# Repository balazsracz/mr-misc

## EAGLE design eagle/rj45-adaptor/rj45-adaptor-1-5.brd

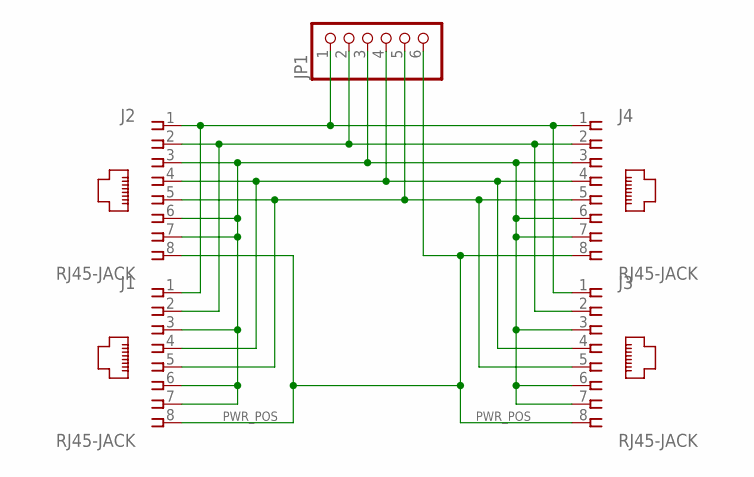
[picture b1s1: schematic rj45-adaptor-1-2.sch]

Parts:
J1, J2, J3, J4: RJ45-JACK; RJ45-PULSE-E5J88
JP1: PINHD-1X6; 1X06

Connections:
ALT1: J1.4, J2.4, J3.4, J4.4, JP1.4
ALT2: J1.5, J2.5, J3.5, J4.5, JP1.5
CANH: J1.1, J2.1, J3.1, J4.1, JP1.1
CANL: J1.2, J2.2, J3.2, J4.2, JP1.2
GND: J1.3, J1.6, J1.7, J2.3, J2.6, J2.7, J3.3, J3.6, J3.7, J4.3, J4.6, J4.7, JP1.3
PWR_POS: J1.8, J2.8, J3.8, J4.8, JP1.6

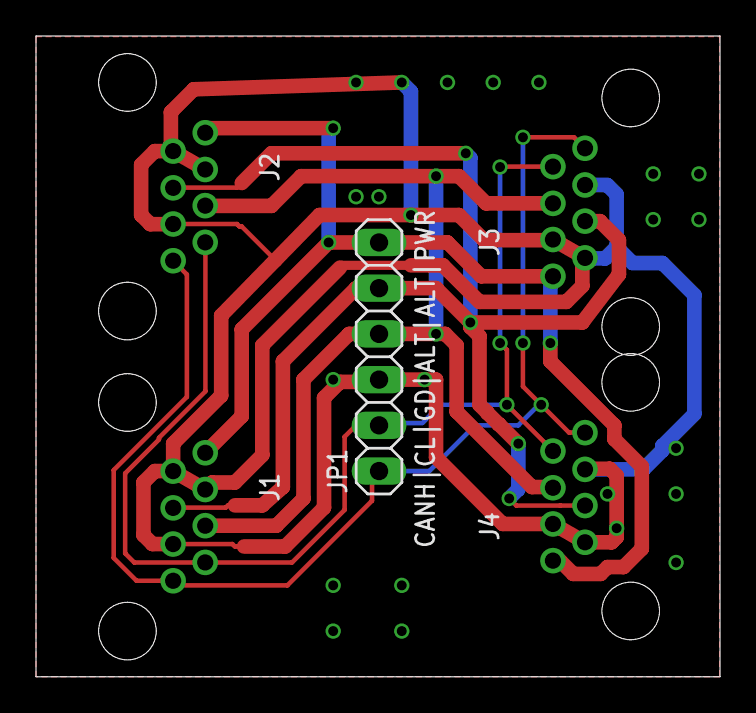
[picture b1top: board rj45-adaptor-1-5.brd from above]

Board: 2 copper layers, 38.0 x 35.6 mm, 5 parts (0 on the bottom side), 6 nets.

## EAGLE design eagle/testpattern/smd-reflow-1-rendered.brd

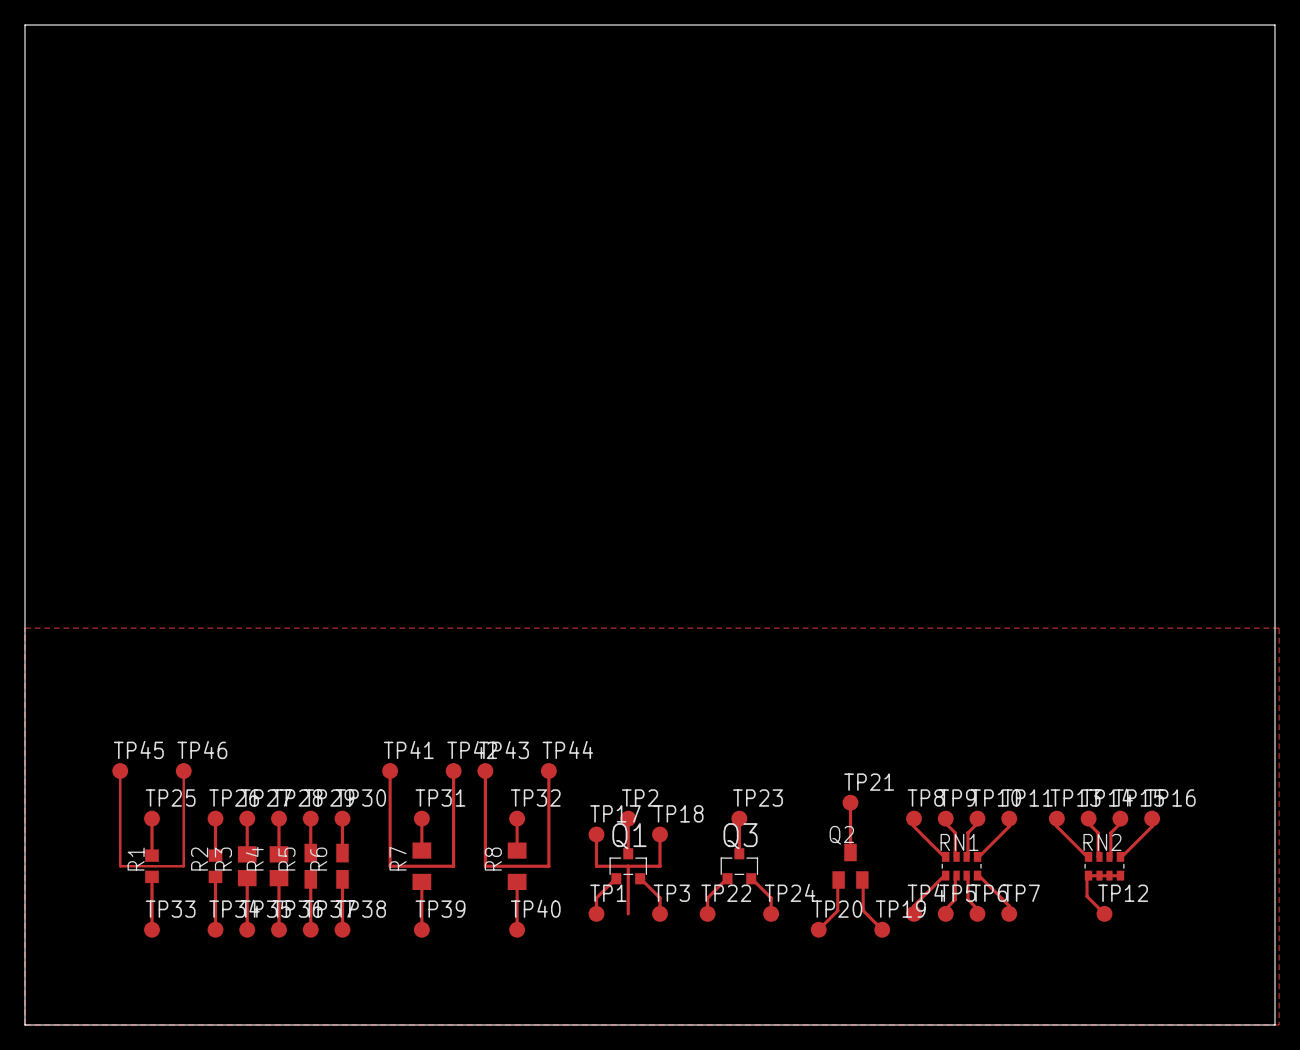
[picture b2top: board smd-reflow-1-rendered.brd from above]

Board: 2 copper layers, 100.0 x 80.0 mm, 59 parts (0 on the bottom side), 42 nets.

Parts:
Q1, Q3: IRLML2502; MICRO3
Q2: BSS84; SOT23
R1, R2: R0603
R3, R4: R0805
R5, R6: R0805W
R7, R8: R-EU; R0805H
RN1, RN2: EXB38V
TP1, TP2, TP3, TP4, TP5, TP6, TP7, TP8, TP9, TP10, TP11, TP12, TP13, TP14, TP15, TP16, TP17, TP18, TP19, TP20, TP21, TP22, TP23, TP24, TP25, TP26, TP27, TP28, TP29, TP30, TP31, TP32, TP33, TP34, TP35, TP36, TP37, TP38, TP39, TP40, TP41, TP42, TP43, TP44, TP45, TP46: TPB1,27; B1,27

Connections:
unnamed: RN1.1, TP4.TP
unnamed: RN1.2, TP5.TP
unnamed: RN1.3, TP6.TP
unnamed: RN1.4, TP7.TP
unnamed: RN1.8, TP8.TP
unnamed: RN1.7, TP9.TP
unnamed: RN1.6, TP10.TP
unnamed: RN1.5, TP11.TP
unnamed: RN2.1, RN2.2, RN2.3, RN2.4, TP12.TP
unnamed: RN2.8, TP13.TP
unnamed: RN2.7, TP14.TP
unnamed: RN2.6, TP15.TP
unnamed: RN2.5, TP16.TP
unnamed: Q1.3, TP2.TP
unnamed: Q1.1, TP1.TP
unnamed: Q1.2, TP3.TP
unnamed: TP17.TP, TP18.TP
unnamed: Q2.2, TP19.TP
unnamed: Q2.1, TP20.TP
unnamed: Q2.3, TP21.TP
unnamed: Q3.3, TP23.TP
unnamed: Q3.1, TP22.TP
unnamed: Q3.2, TP24.TP
unnamed: R1.2, TP25.TP
unnamed: R2.2, TP26.TP
unnamed: R3.2, TP27.TP
unnamed: R4.2, TP28.TP
unnamed: R6.2, TP30.TP
unnamed: R5.2, TP29.TP
unnamed: R7.2, TP31.TP
unnamed: R8.2, TP32.TP
unnamed: R1.1, TP33.TP
unnamed: R2.1, TP34.TP
unnamed: R3.1, TP35.TP
unnamed: R4.1, TP36.TP
unnamed: R5.1, TP37.TP
unnamed: R6.1, TP38.TP
unnamed: R7.1, TP39.TP
unnamed: R8.1, TP40.TP
unnamed: TP41.TP, TP42.TP
unnamed: TP43.TP, TP44.TP
unnamed: TP45.TP, TP46.TP
